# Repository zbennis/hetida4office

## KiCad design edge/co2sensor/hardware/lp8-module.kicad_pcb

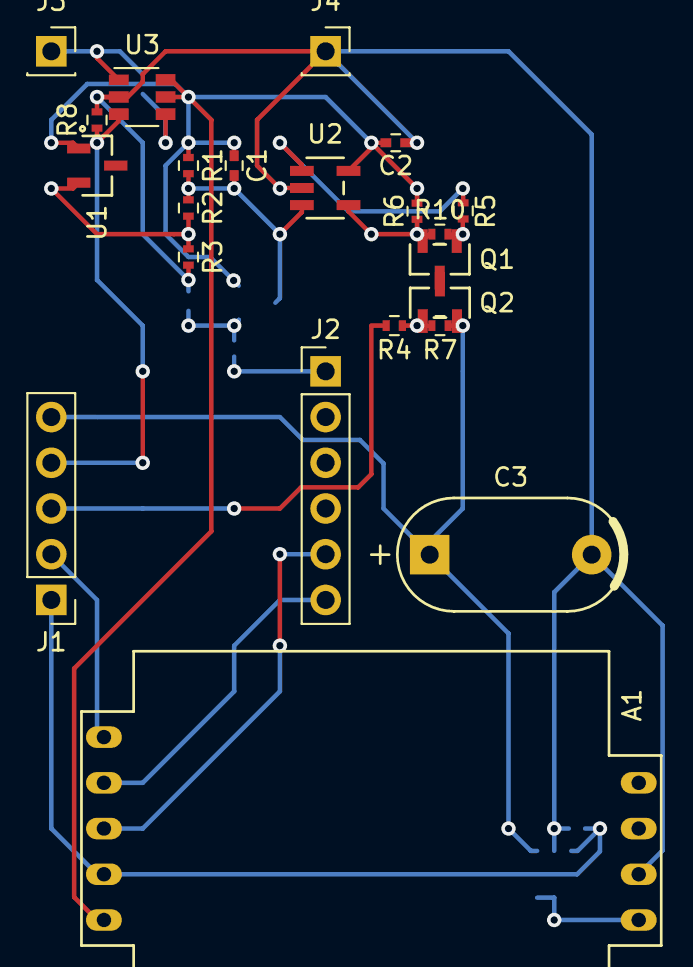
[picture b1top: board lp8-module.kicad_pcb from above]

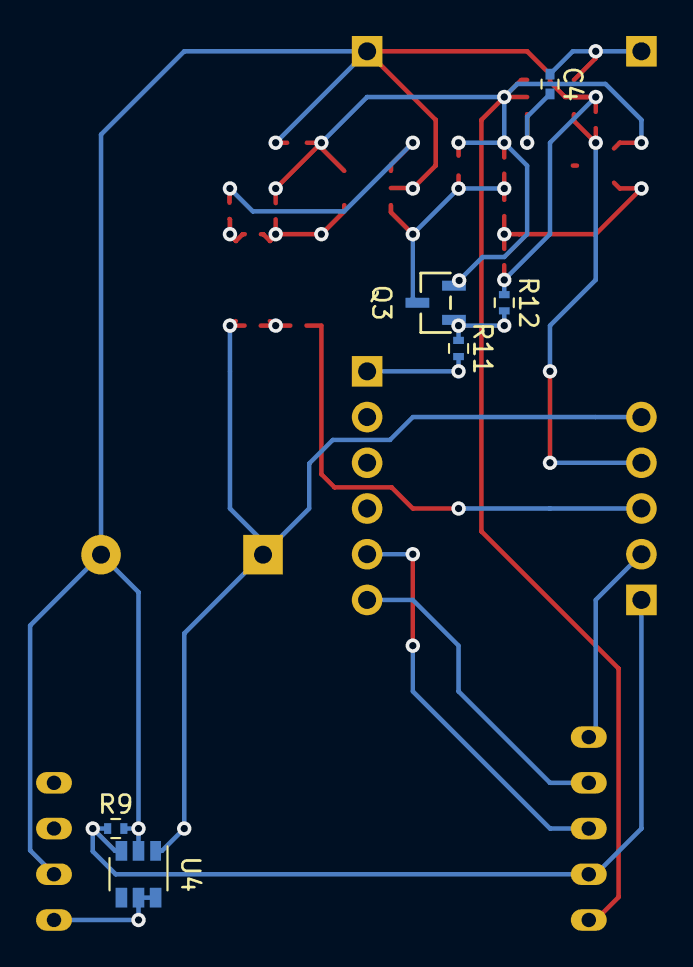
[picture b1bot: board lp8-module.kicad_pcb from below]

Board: 2 copper layers, 28 parts (6 on the bottom side), 21 nets.

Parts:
A1: SenseAir-LP8; LP8
C1: 100n; C_0402
C2: 10n; C_0402
C3: 470m; AVX_SCM_L14.00_W6.30
C4: 470p; C_0402
J1: Conn_01x05_Male; PinHeader_1x05_P2.54mm_Vertical
J2: Conn_01x06_Male; PinHeader_1x06_P2.54mm_Vertical
J3, J4: Conn_01x01_Male; PinSocket_1x01_P2.54mm_Vertical
Q1, Q2, Q3: PMOS-SI2315BDS-T1-E3; SI2315BDS-T1-E3
R1: 82k; R_0402
R2: 910k; R_0402
R3: 249k; R_0402
R4, R5, R11: 1k1; R_0402
R6: 500m; R_0402
R7, R8, R9, R10, R12: 100k; R_0402
U1: MAX6006/LT1634; 21-0051H
U2: MCP6041T-EOT; MCP6041T-E&slash_OT
U3, U4: TPS22917; SOT-23-6

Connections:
/3V3: C4.1, J3.1, U3.1
/LP8/LP8_3V3: A1.2.1, C1.1, C2.2, Q3.2, R1.1, R6.1, U1.1, U2.5, U3.5, U3.6
/LP8/V+: C1.2, Q3.3, R1.2, R2.1, U2.3
/LP8/V-: Q1.2, R6.2, R10.1, U2.4
/LP8_EN_CHARGE: J2.1, R11.2
/LP8_EN_MEAS: A1.2.2, J1.1, R9.1, U4.3
/LP8_EN_PWR: J1.4, R8.2, U3.3
/LP8_EN_REV_BLOCK: J1.3, R4.2
/LP8_MEAS_RDY: A1.2.5, J1.2
/LP8_VCAP: C3.1, J1.5, Q2.2, R7.1, U4.1
/RxD: A1.2.4, J2.6
/TxD: A1.2.3, J2.5
GND: A1.1.2, C2.1, C3.2, J4.1, R3.2, R8.1, R9.2, R12.1, U2.2, U3.2, U4.2
unnamed: A1.1.1, U4.5, U4.6
unnamed: C4.2, U3.4
unnamed: Q1.1, R5.1, R10.2
unnamed: Q1.3, Q2.3
unnamed: Q2.1, R4.1, R7.2
unnamed: Q3.1, R11.1, R12.2
unnamed: R2.2, R3.1, U1.2
unnamed: R5.2, U2.1

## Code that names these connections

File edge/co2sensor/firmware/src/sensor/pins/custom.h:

#ifndef PINS_H
#define PINS_H

#include "hal/nrf_gpio.h"
#include <nrfx_lpcomp.h>

#define PIN_RX_D0 NRF_GPIO_PIN_MAP(0, 30)
#define PIN_TX_D1 NRF_GPIO_PIN_MAP(1, 9)

#define PIN_D2 NRF_GPIO_PIN_MAP(1, 11)
#define PIN_D3 NRF_GPIO_PIN_MAP(1, 10)
#define PIN_D4 NRF_GPIO_PIN_MAP(0, 3)
#define PIN_D6 NRF_GPIO_PIN_MAP(1, 13)
#define PIN_D7 NRF_GPIO_PIN_MAP(0, 9)
#define PIN_A5_LPCOMP NRF_LPCOMP_INPUT_0 // AIN0 -- reserved for LPCOMP peripheral

#define PIN_LED1 NRF_GPIO_PIN_MAP(0, 5)
#define PIN_LED2 NRF_GPIO_PIN_MAP(0, 6)
#define PIN_SWITCH1 NRF_GPIO_PIN_MAP(0, 10)
#define PIN_SWITCH2 NRF_GPIO_PIN_MAP(0, 31)

#define PIN_SDA NRF_GPIO_PIN_MAP(0, 13)
#define PIN_SCL NRF_GPIO_PIN_MAP(0, 4)

#define PIN_MEAS_BAT NRF_GPIO_PIN_MAP(0, 28)
#define PIN_nEN_MEAS_BAT NRF_GPIO_PIN_MAP(0, 29)


// UART
#define PIN_UART_RX PIN_RX_D0
#define PIN_UART_TX PIN_TX_D1

// LP8
#define PIN_LP8_EN_CHARGE PIN_D7 // digital out, D0S1, no pull
#define PIN_LP8_EN_REV_BLOCK PIN_D4 // digital out, S0D1, no pull
#define PIN_LP8_EN_PWR PIN_D6 // digital out, D0S1, no pull
#define PIN_LP8_EN_MEAS PIN_D2 // digital out, D0S1, no pull
#define PIN_LP8_VCAP_LPCOMP PIN_A5_LPCOMP // analog in
#define PIN_LP8_MEAS_RDY PIN_D3 // digital in
#define PIN_LP8_RXD PIN_UART_TX // UART
#define PIN_LP8_TXD PIN_UART_RX // UART

// I2C
#define PIN_I2C_SDA PIN_SDA
#define PIN_I2C_SCL PIN_SCL

// BAT
#define PIN_BAT_MEAS PIN_MEAS_BAT // digital out, S0D1, no pull
#define PIN_BAT_nEN_MEAS PIN_nEN_MEAS_BAT // analog in

#define NUM_DIGITAL_IN 1 // required to configure resources for GPIOTE event listeners

#endif // PINS_H

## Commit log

2020-11-14 initial directory structure
2020-11-15 added hardware files
2020-11-15 Azure terraform basic script
2020-11-15 add stop bits to uarte driver
2020-11-15 added firmware
2020-11-15 add mqttsn driver
2020-11-15 add NCP project
2020-11-15 add cli
2020-11-16 enable logging of multiple measures
2020-11-16 stabilize sensor readings when packets are dropped
2020-11-16 updated terraform config
2020-11-16 add local dev docker-compose file
2020-11-17 initial version of core microservices: mqtt client :: mqtt-to-kafka-to-timescaledb gateway
2020-11-17 add hive, timescaledb, kafka, zookeeper
2020-11-17 remind myself of stability improvement
2020-11-17 remove obsolete keepme files
2020-11-17 adapt README to full installation procedure
2020-11-17 complete terraform module config
2020-11-17 infrastructor for mqtt to db connectors
2020-11-17 add profiles local, docker and production
2020-11-17 fix kafka borker host for prod
2020-11-17 fix kafka advertised listener port for docker profiles, rename mservices docker-files for docker-compose
2020-11-18 add fake sensors measurement publisher client, several refactorings
2020-11-18 tune database for timeseries and add flyway migration scripts
2020-11-19 Integrate travis ci and push images to docker hub (#9)
    * integrate travis ci builds and push images to docker hub
    * fix secures, remove deprecated entries
    * try to fix build
2020-11-19 Fix build and push latest images to docker hub (#10)
    * integrate travis ci builds and push images to docker hub
    * fix secures, remove deprecated entries
    * try to fix build
    * fix file path for docker build and push
    * Create README.md
    * try to fix docker build and push
2020-11-19 replace fork build status with organisation build status
2020-11-21 configure kafka for k8s, add grafana
2020-11-22 stabilize sensor
2020-11-22 publish all measurements
2020-11-22 automatic versioning of docker images
2020-11-23 Refactoring (#11)
    * integrate travis ci builds and push images to docker hub
    * fix secures, remove deprecated entries
    * try to fix build
    * fix file path for docker build and push
    * Create README.md
    * try to fix docker build and push
2020-11-29 add qspi reset for low energy mode
2020-11-29 added background calibration capability
2020-12-26 fix SDK bug: dequeuing topic registration package after reading it
2020-12-26 hardware upgrade
2020-12-26 fix typo
2020-12-26 fix race condition in gpio actor
2020-12-26 mqttsn actor: fix various bugs and race conditions
2020-12-26 add fab files
2020-12-26 add some reasonable formatting
2020-12-26 add battery measurement
2020-12-26 various minor fixes
2020-12-26 fix execution flag of build script
2020-12-26 bump version
2020-12-26 simplify build
2020-12-26 clean up infrastructure scripts
2020-12-26 fix kafka consumer host config
2020-12-27 adjust settings
